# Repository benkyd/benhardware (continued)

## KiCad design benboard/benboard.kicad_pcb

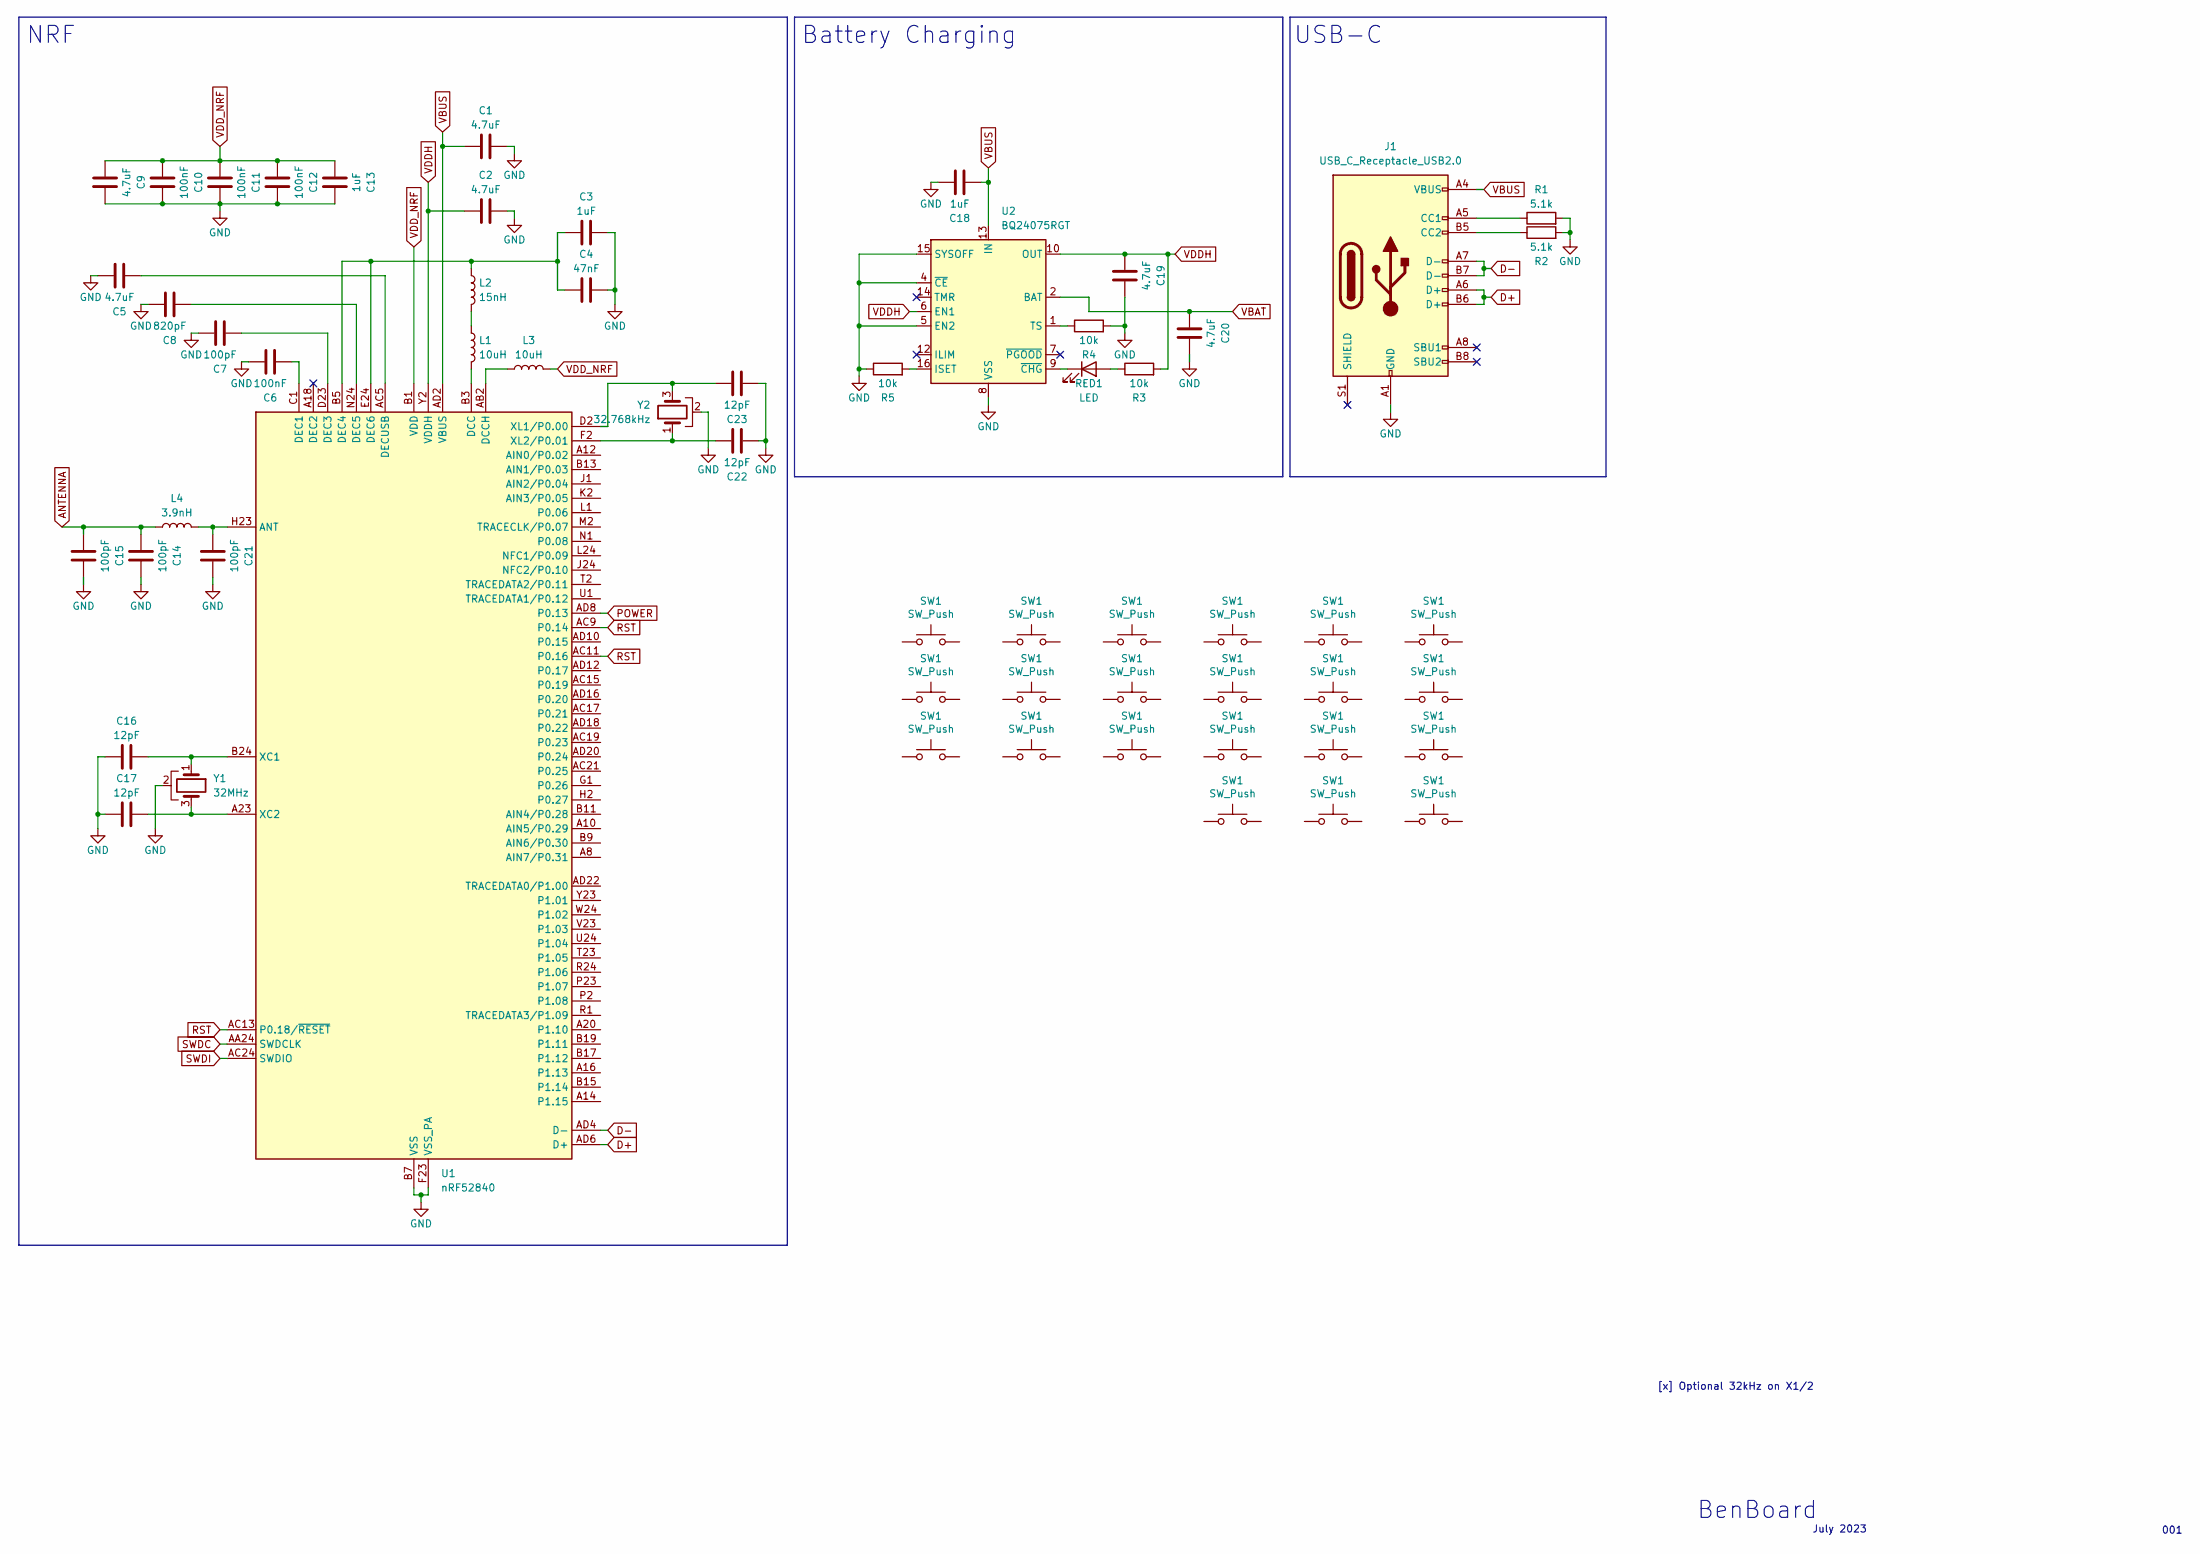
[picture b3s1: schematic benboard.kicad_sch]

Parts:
C1, C2, C5, C9, C19, C20: 4.7uF; C_0603_1608Metric
C3, C13, C18: 1uF; C_0603_1608Metric
C4: 47nF; C_0603_1608Metric
C6, C10, C11, C12: 100nF; C_0603_1608Metric
C7, C14, C15, C21: 100pF; C_0603_1608Metric
C8: 820pF; C_0603_1608Metric
C16, C17, C22, C23: 12pF; C_0603_1608Metric
J1: USB_C_Receptacle_USB2.0; USB_C_Receptacle_G-Switch_GT-USB-7010ASV
L1, L3: 10uH; L_0603_1608Metric
L2: 15nH; L_0603_1608Metric
L4: 3.9nH; L_0603_1608Metric
R1, R2: 5.1k; R_0603_1608Metric
R3, R4, R5: 10k; R_0603_1608Metric
RED1: LED; LED_0805_2012Metric
SW1: SW_Push; Kailh_socket_MX_optional_reversible
U1: nRF52840; Nordic_AQFN-73-1EP_7x7mm_P0.5mm
U2: BQ24075RGT; VQFN-16-1EP_3x3mm_P0.5mm_EP1.6x1.6mm
Y1: 32MHz; Crystal_SMD_SeikoEpson_FA238V-4Pin_3.2x2.5mm
Y2: 32.768kHz; Crystal_SMD_SeikoEpson_FA238V-4Pin_3.2x2.5mm

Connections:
ANTENNA: C14.1, C15.1, L4.1
D+: J1.A6 (D+), J1.B6 (D+), U1.AD6 (D+)
D-: J1.A7 (D-), J1.B7 (D-), U1.AD4 (D-)
GND: C1.2, C2.2, C3.2, C4.2, C5.2, C6.2, C7.2, C8.2, C9.2, C10.2, C11.2, C12.2, C13.2, C14.2, C15.2, C16.1, C17.1, C18.2, C19.2, C20.2, C21.2, C22.1, C23.1, J1.A1 (GND), J1.A12 (GND), J1.B1 (GND), J1.B12 (GND), R1.2, R2.2, R4.2, R5.1, U1.B7 (VSS), U1.EP (VSS), U1.F23 (VSS_PA), U2.4 (~CE), U2.5 (EN2), U2.8 (VSS), U2.15 (SYSOFF), U2.17 (VSS), Y1.2, Y2.2
unnamed: J1.A5 (CC1), R1.1
unnamed: J1.B5 (CC2), R2.1
unnamed: L1.1, L2.2
unnamed: R3.1, RED1.2 (A)
unnamed: RED1.1 (K), U2.9 (~CHG)
unnamed: C21.1, L4.2, U1.H23 (ANT)
unnamed: L1.2, U1.B3 (DCC)
unnamed: L3.1, U1.AB2 (DCCH)
unnamed: C6.1, U1.C1 (DEC1)
unnamed: C7.1, U1.D23 (DEC3)
unnamed: C3.1, C4.1, L2.1, U1.B5 (DEC4), U1.E24 (DEC6)
unnamed: C8.1, U1.N24 (DEC5)
unnamed: C5.1, U1.AC5 (DECUSB)
unnamed: C16.2, U1.B24 (XC1), Y1.1
unnamed: C17.2, U1.A23 (XC2), Y1.3
unnamed: C23.2, U1.D2 (XL1/P0.00), Y2.3
unnamed: C22.2, U1.F2 (XL2/P0.01), Y2.1
unnamed: R5.2, U2.16 (ISET)
unnamed: R4.1, U2.1 (TS)
POWER: U1.AD8 (P0.13)
RST: U1.AC9 (P0.14), U1.AC11 (P0.16), U1.AC13 (P0.18/~RESET)
SWDC: U1.AA24 (SWDCLK)
SWDI: U1.AC24 (SWDIO)
VBAT: C20.1, U2.2 (BAT), U2.3 (BAT)
VBUS: C1.1, C18.1, J1.A4 (VBUS), J1.A9 (VBUS), J1.B4 (VBUS), J1.B9 (VBUS), U1.AD2 (VBUS), U2.13 (IN)
VDDH: C2.1, C19.1, R3.2, U1.Y2 (VDDH), U2.6 (EN1), U2.10 (OUT), U2.11 (OUT)
VDD_NRF: C9.1, C10.1, C11.1, C12.1, C13.1, L3.2, U1.A22 (VDD), U1.AD14 (VDD), U1.AD23 (VDD), U1.B1 (VDD), U1.W1 (VDD)

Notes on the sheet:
[x] Optional 32kHz on X1/2
USB-C
001
NRF
BenBoard
Battery Charging
July 2023

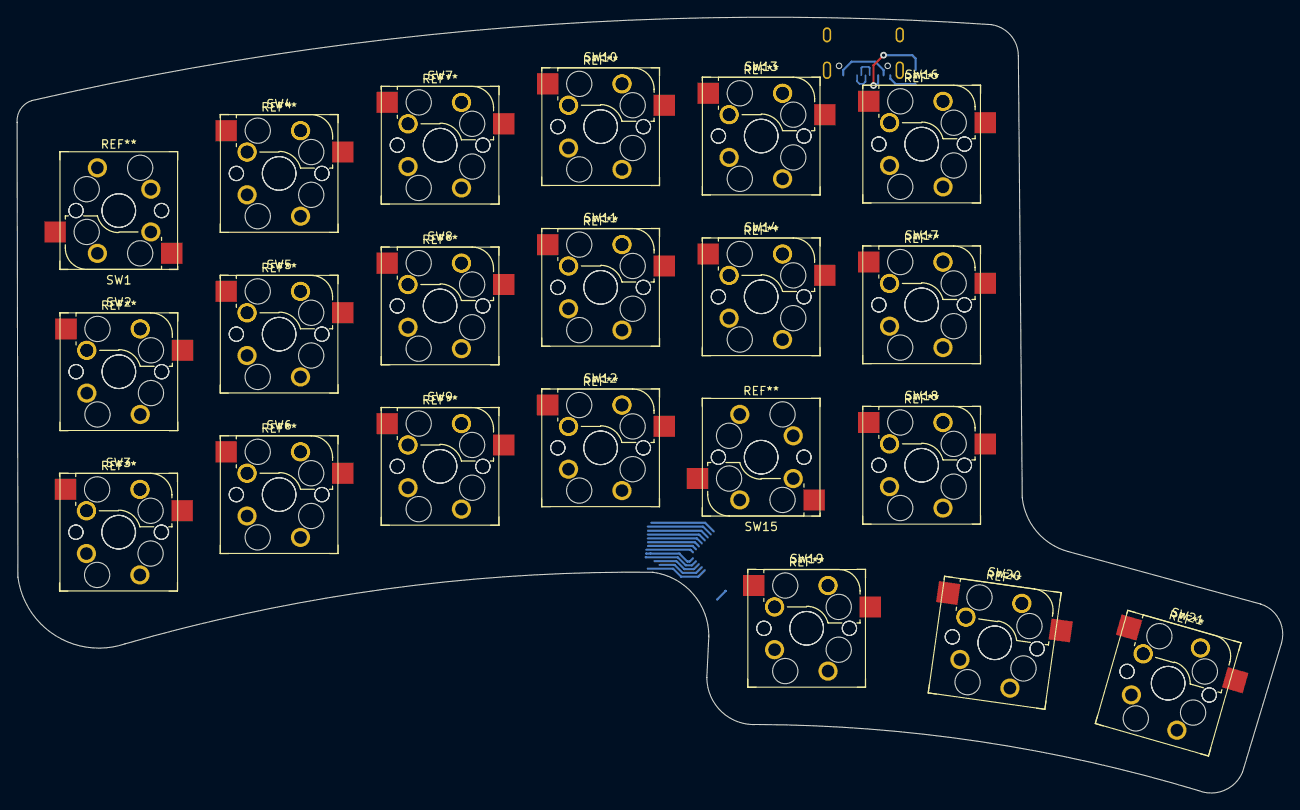
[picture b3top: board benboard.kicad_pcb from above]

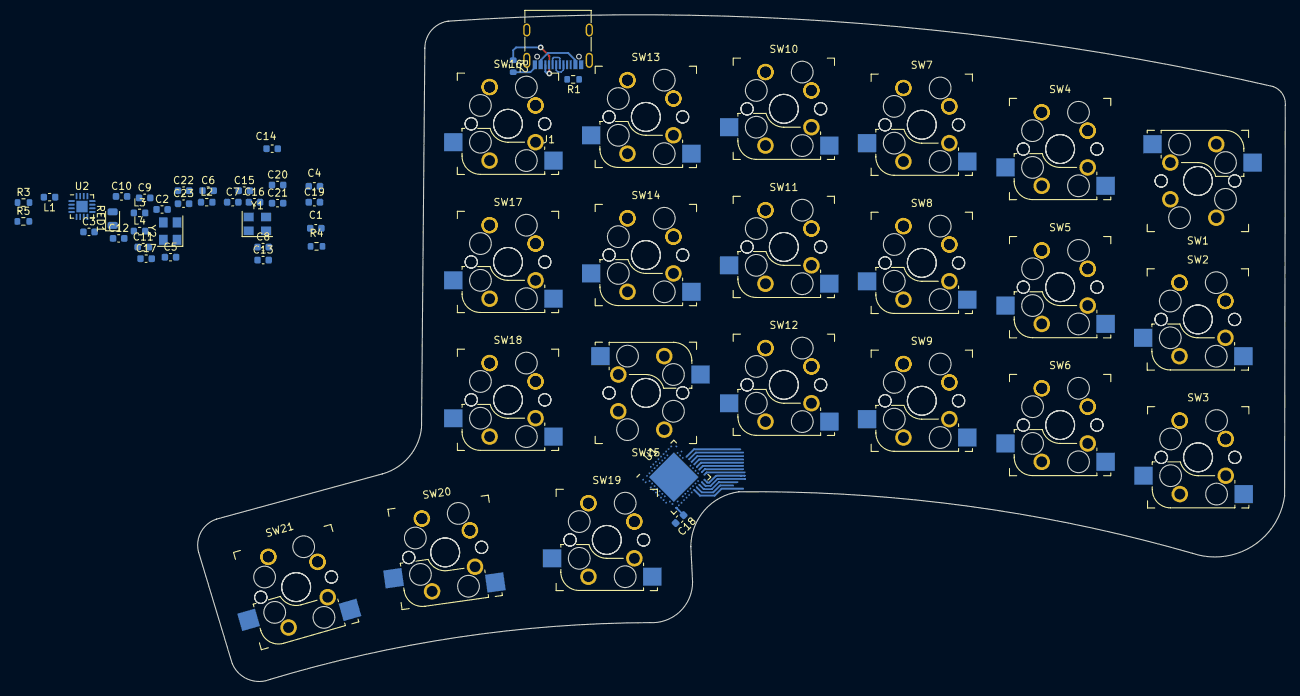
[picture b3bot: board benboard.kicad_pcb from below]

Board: 4 copper layers, 150.3 x 92.1 mm, 59 parts (38 on the bottom side), 28 nets.

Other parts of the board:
SW2, SW3, SW4, SW5, SW6, SW7, SW8, SW9, SW10, SW11, SW12, SW13, SW14, SW15, SW16, SW17, SW18, SW19, SW20, SW21: SW_Push; Kailh_socket_MX_optional_reversible

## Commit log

2023-07-20 init
2023-07-20 Swweeep base and benboard 1
2023-07-20 keyboad
2023-07-21 awesome
2023-07-26 epic
2023-07-26 BenBoard has changed ownership
2025-03-17 hdd backplane
2025-03-31 HDD Update and Meshtastic board
2025-04-01 Meshtastic
2025-04-01 Swap switch
2025-04-01 power switching
2025-04-03 Most component selection
2025-04-03 better part selection
2025-04-03 small rev
2025-04-03 test
2025-04-04 routing
2025-04-08 Ben Labs Node 30.5dBm rev A in production
2025-04-10 toaster
2025-04-10 remove old
2025-05-07 Backplane
